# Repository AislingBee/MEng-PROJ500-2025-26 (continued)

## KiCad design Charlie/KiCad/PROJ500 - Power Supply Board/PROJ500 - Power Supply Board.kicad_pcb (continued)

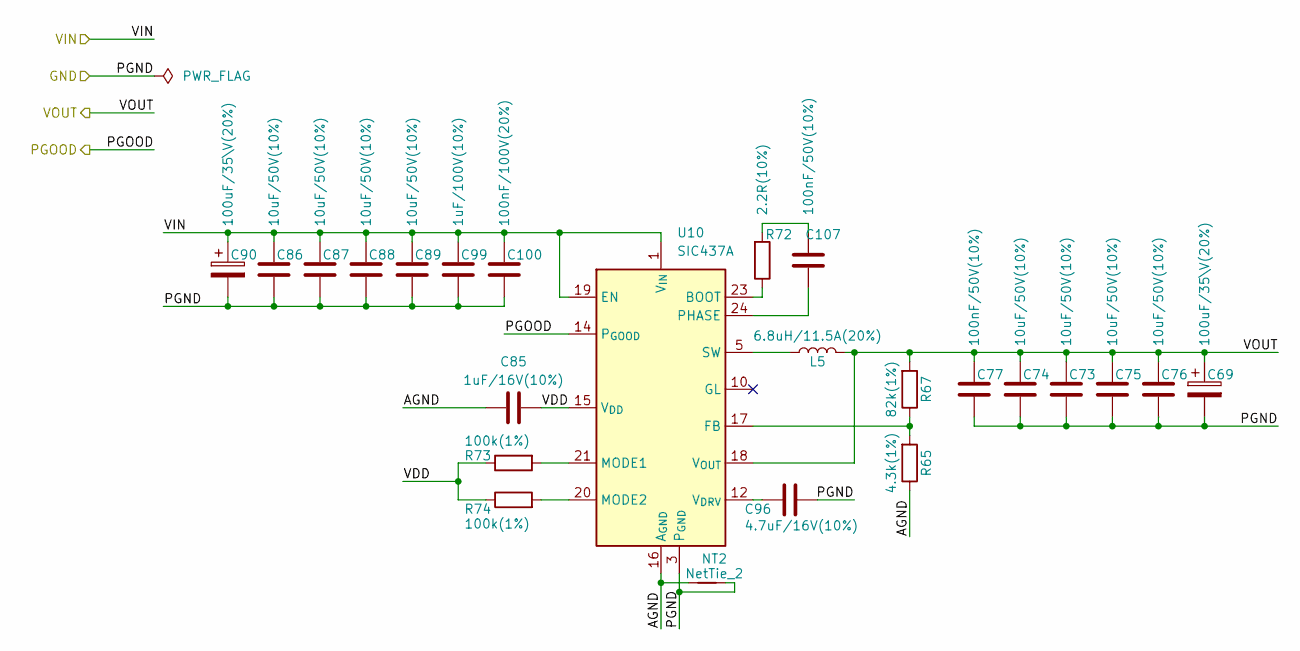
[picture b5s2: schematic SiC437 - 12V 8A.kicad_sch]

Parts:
C69, C90: 100uF/35\V(20%); CAPAE830X700N
C73, C74, C75, C76, C86, C87, C88, C89: 10uF/50V(10%); C_1206_3216Metric
C77, C107: 100nF/50V(10%); C_0402_1005Metric
C85: 1uF/16V(10%); C_0603_1608Metric
C96: 4.7uF/16V(10%); C_0805_2012Metric
C99: 1uF/100V(10%); C_0603_1608Metric
C100: 100nF/100V(20%); C_0603_1608Metric
L5: 6.8uH/11.5A(20%); INDPM135125X650N
NT2: NetTie_2; NetTie-2_SMD_Pad0.5mm
R65: 4.3k(1%); R_0402_1005Metric
R67: 82k(1%); R_0402_1005Metric
R72: 2.2R(10%); R_0402_1005Metric
R73, R74: 100k(1%); R_0402_1005Metric
U10: SIC437A; Vishay_PowerPAK_MLP44-24L

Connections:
24V_SW: C86.1, C87.1, C88.1, C89.1, C90.1, C99.1, C100.1, U10.1 (V_{IN}), U10.2 (V_{IN}), U10.19 (EN), U10.22 (V_{IN}), U10.26 (V_{IN}); also elsewhere on the board
/12V_SW_PGOOD: U10.14 (P_{GOOD}); also elsewhere on the board
/I_12V_SW_P: C69.1, C73.1, C74.1, C75.1, C76.1, C77.1, L5.2, R67.2, U10.18 (V_{OUT}); also elsewhere on the board
/SiC437 - 12V 8A/AGND: C85.1, NT2.1, R65.1, U10.16 (A_{GND}), U10.25 (A_{GND})
/SiC437 - 12V 8A/VDD: C85.2, R73.1, R74.1, U10.15 (V_{DD})
GNDPWR: C69.2, C73.2, C74.2, C75.2, C76.2, C77.2, C86.2, C87.2, C88.2, C89.2, C90.2, C96.2, C99.2, C100.2, NT2.2, U10.3 (P_{GND}), U10.4 (P_{GND}), U10.13 (P_{GND}), U10.27 (P_{GND}); also elsewhere on the board
unnamed: C107.2, R72.2
unnamed: L5.1, U10.5 (SW), U10.6 (SW), U10.7 (SW), U10.8 (SW), U10.9 (SW)
unnamed: R72.1, U10.23 (BOOT)
unnamed: R65.2, R67.1, U10.17 (FB)
unnamed: R73.2, U10.21 (MODE1)
unnamed: R74.2, U10.20 (MODE2)
unnamed: C107.1, U10.24 (PHASE)
unnamed: C96.1, U10.12 (V_{DRV})

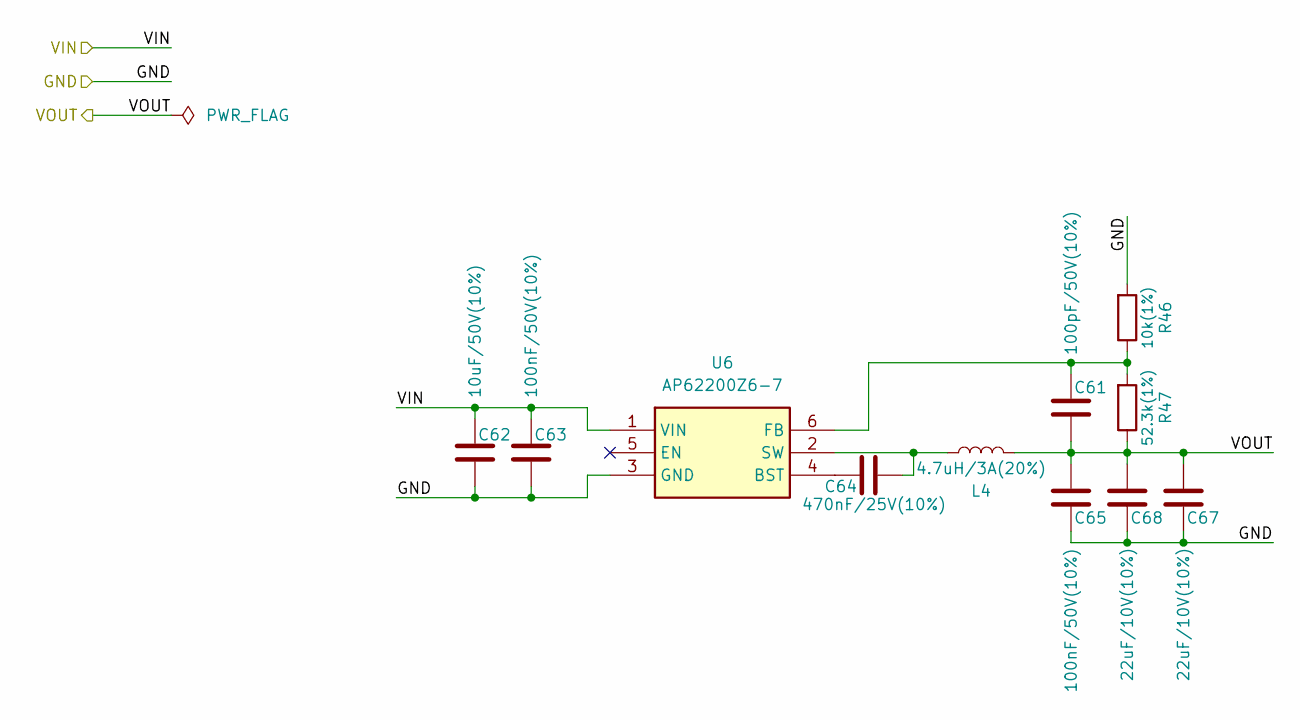
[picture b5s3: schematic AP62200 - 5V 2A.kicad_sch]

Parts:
C61: 100pF/50V(10%); C_0402_1005Metric
C62: 10uF/50V(10%); C_1206_3216Metric
C63, C65: 100nF/50V(10%); C_0402_1005Metric
C64: 470nF/25V(10%); C_0603_1608Metric
C67, C68: 22uF/10V(10%); C_0805_2012Metric
L4: 4.7uH/3A(20%); ASPI-4030S
R46: 10k(1%); R_0402_1005Metric
R47: 52.3k(1%); R_0402_1005Metric
U6: AP62200Z6-7; SOT-563; Mouser Part Number 621-AP62200Z6-7

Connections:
+5V: C61.2, C65.1, C67.1, C68.1, L4.1, R47.1; also elsewhere on the board
+12V: C62.1, C63.1, U6.1 (VIN); also elsewhere on the board
GNDPWR: C62.2, C63.2, C65.2, C67.2, C68.2, R46.2, U6.3 (GND); also elsewhere on the board
unnamed: C64.1, U6.4 (BST)
unnamed: C61.1, R46.1, R47.2, U6.6 (FB)
unnamed: C64.2, L4.2, U6.2 (SW)

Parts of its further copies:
C84, C93: 22uF/10V(10%); C_0805_2012Metric
C91: 10uF/50V(10%); C_1206_3216Metric
C98, C102: 100nF/50V(10%); C_0402_1005Metric
C109: 100pF/50V(10%); C_0402_1005Metric
C110: 470nF/25V(10%); C_0603_1608Metric
L6: 4.7uH/3A(20%); ASPI-4030S
R70: 10k(1%); R_0402_1005Metric
R80: 52.3k(1%); R_0402_1005Metric
U13: AP62200Z6-7; SOT-563; Mouser Part Number 621-AP62200Z6-7

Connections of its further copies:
5V_SW: C84.1, C93.1, C98.1, C109.2, L6.1, R80.1; also elsewhere on the board
12V_SW: C91.1, C102.1, U13.1 (VIN); also elsewhere on the board
GNDPWR: C84.2, C91.2, C93.2, C98.2, C102.2, R70.2, U13.3 (GND); also elsewhere on the board
unnamed: C110.1, U13.4 (BST)
unnamed: C109.1, R70.1, R80.2, U13.6 (FB)
unnamed: C110.2, L6.2, U13.2 (SW)

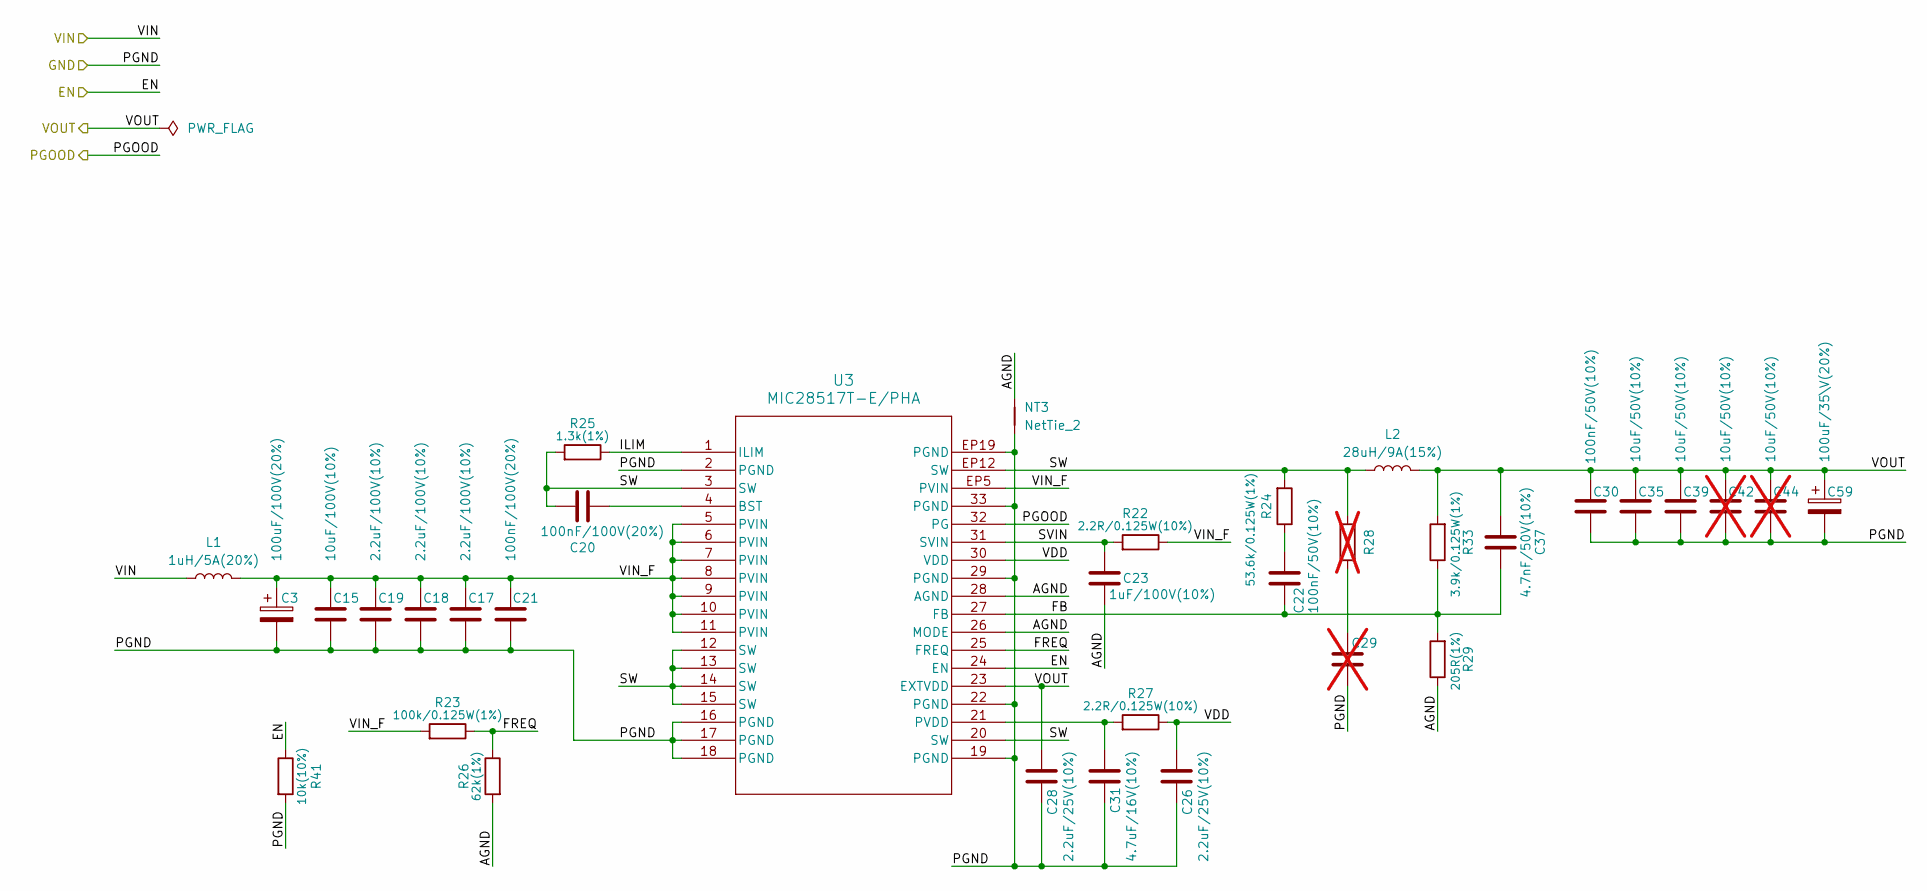
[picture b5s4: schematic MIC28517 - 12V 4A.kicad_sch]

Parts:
C3: 100uF/100V(20%); CP_Radial_D10.0mm_P5.00mm
C15: 10uF/100V(10%); C_1210_3225Metric
C17, C18, C19: 2.2uF/100V(10%); C_0805_2012Metric
C20, C21: 100nF/100V(20%); C_0603_1608Metric
C22, C30: 100nF/50V(10%); C_0402_1005Metric
C23: 1uF/100V(10%); C_0603_1608Metric
C26, C28: 2.2uF/25V(10%); C_0805_2012Metric
C29: C_0603_1608Metric; not fitted
C31: 4.7uF/16V(10%); C_0805_2012Metric
C35, C39: 10uF/50V(10%); C_1206_3216Metric
C37: 4.7nF/50V(10%); C_0402_1005Metric
C42, C44: 10uF/50V(10%); C_1206_3216Metric; not fitted
C59: 100uF/35\V(20%); CAPAE830X700N
L1: 1uH/5A(20%); L_1008_2520Metric
L2: 28uH/9A(15%); PA2729283NL
NT3: NetTie_2; NetTie-2_SMD_Pad0.5mm
R22: 2.2R/0.125W(10%); R_0805_2012Metric
R23: 100k/0.125W(1%); R_0603_1608Metric
R24: 53.6k/0.125W(1%); R_0805_2012Metric
R25: 1.3k(1%); R_0402_1005Metric
R26: 62k(1%); R_0402_1005Metric
R27: 2.2R/0.125W(10%); R_0603_1608Metric
R28: R_0805_2012Metric; not fitted
R29: 205R(1%); R_0402_1005Metric
R33: 3.9k/0.125W(1%); R_0603_1608Metric
R41: 10k(10%); R_0402_1005Metric
U3: MIC28517T-E/PHA; VQFN32_6X6_3EP_PHA_MCH

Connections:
+12V: C28.2, C30.1, C35.1, C37.2, C39.1, C42.1, C44.1, C59.1, L2.1, R33.2, U3.23 (EXTVDD); also elsewhere on the board
/12V_PGOOD: U3.32 (PG); also elsewhere on the board
/AON_EN: R41.1, U3.24 (EN); also elsewhere on the board
/MIC28517 - 12V 4A/AGND: C23.2, NT3.2, R26.2, R29.1, U3.26 (MODE), U3.28 (AGND)
/MIC28517 - 12V 4A/FB: C22.2, C37.1, R29.2, R33.1, U3.27 (FB)
/MIC28517 - 12V 4A/FREQ: R23.1, R26.1, U3.25 (FREQ)
/MIC28517 - 12V 4A/ILIM: R25.1, U3.1 (ILIM)
/MIC28517 - 12V 4A/SVIN: C23.1, R22.2, U3.31 (SVIN)
/MIC28517 - 12V 4A/SW: C20.1, L2.2, R24.2, R25.2, R28.2, U3.3 (SW), U3.12 (SW), U3.13 (SW), U3.14 (SW), U3.15 (SW), U3.20 (SW), U3.EP12 (SW)
/MIC28517 - 12V 4A/VDD: C26.2, R27.1, U3.30 (VDD)
/MIC28517 - 12V 4A/VIN_F: C3.1, C15.1, C17.1, C18.1, C19.1, C21.1, L1.2, R22.1, R23.2, U3.5 (PVIN), U3.6 (PVIN), U3.7 (PVIN), U3.8 (PVIN), U3.9 (PVIN), U3.10 (PVIN), U3.11 (PVIN), U3.EP5 (PVIN)
GNDPWR: C3.2, C15.2, C17.2, C18.2, C19.2, C21.2, C26.1, C28.1, C29.2, C30.2, C31.1, C35.2, C39.2, C42.2, C44.2, C59.2, NT3.1, R41.2, U3.2 (PGND), U3.16 (PGND), U3.17 (PGND), U3.18 (PGND), U3.19 (PGND), U3.22 (PGND), U3.29 (PGND), U3.33 (PGND), U3.EP19 (PGND); also elsewhere on the board
unnamed: C22.1, R24.1
unnamed: C29.1, R28.1
unnamed: C20.2, U3.4 (BST)
unnamed: C31.2, R27.2, U3.21 (PVDD)
VRAW: L1.1; also elsewhere on the board

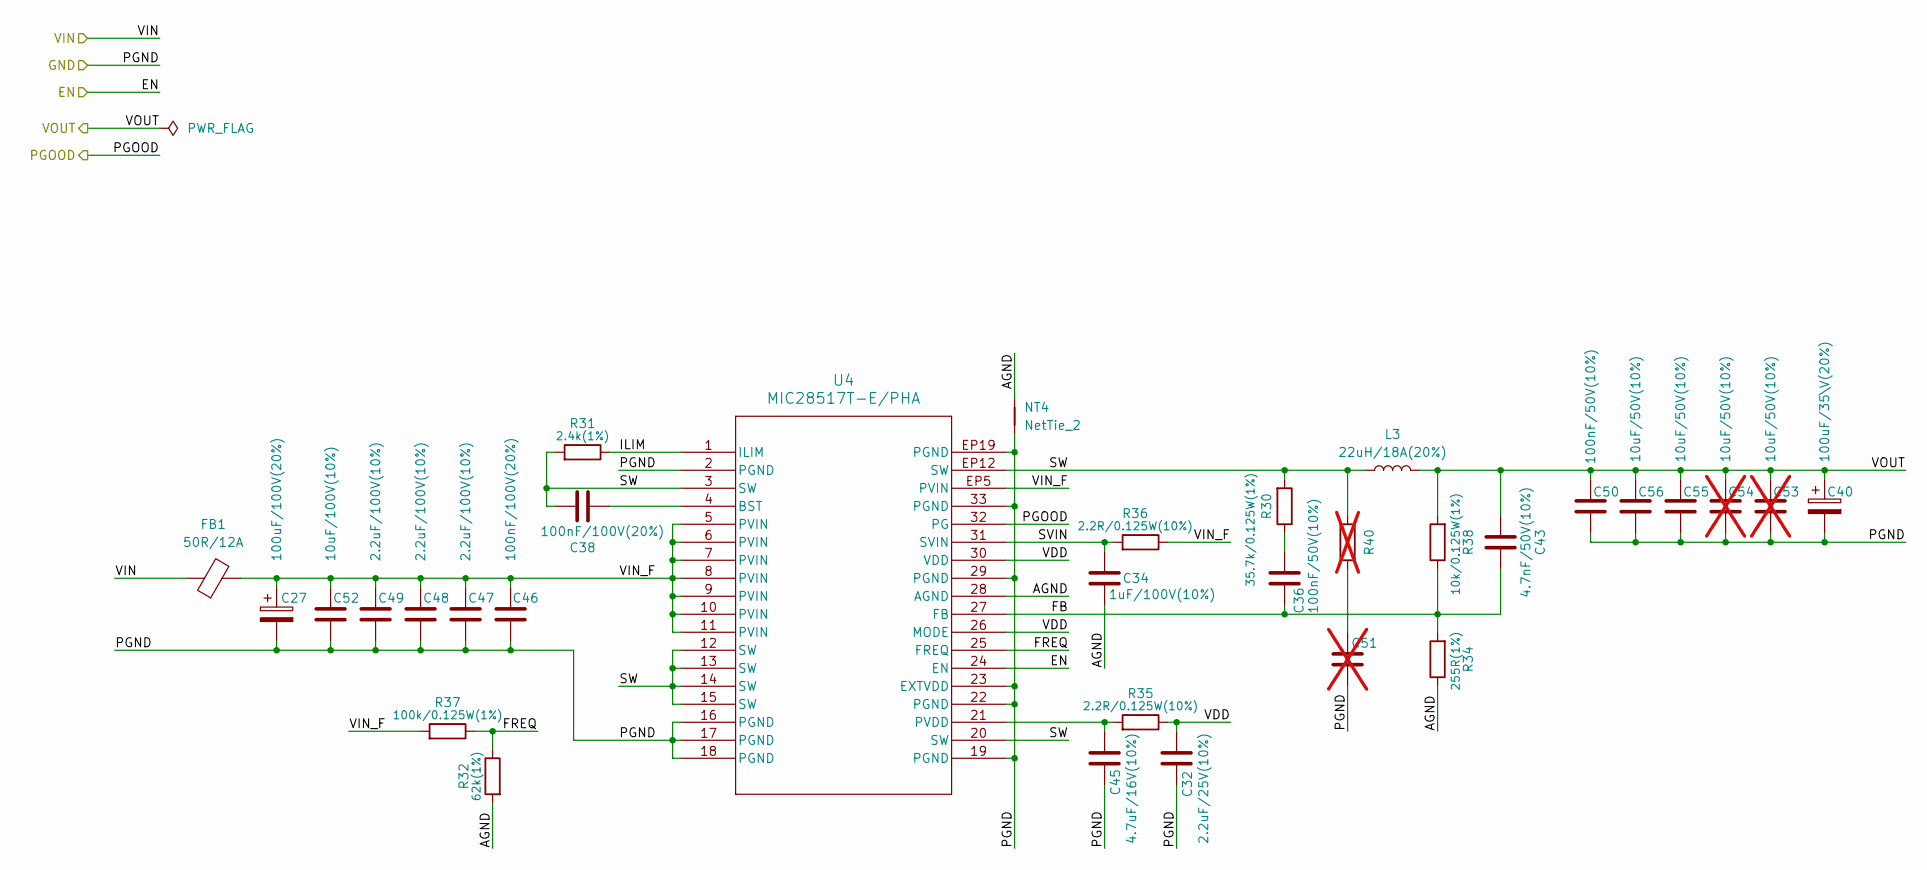
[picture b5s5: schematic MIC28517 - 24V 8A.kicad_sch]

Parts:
C27: 100uF/100V(20%); CP_Radial_D10.0mm_P5.00mm
C32: 2.2uF/25V(10%); C_0805_2012Metric
C34: 1uF/100V(10%); C_0603_1608Metric
C36, C50: 100nF/50V(10%); C_0402_1005Metric
C38, C46: 100nF/100V(20%); C_0603_1608Metric
C40: 100uF/35\V(20%); CAPAE830X700N
C43: 4.7nF/50V(10%); C_0402_1005Metric
C45: 4.7uF/16V(10%); C_0805_2012Metric
C47, C48, C49: 2.2uF/100V(10%); C_0805_2012Metric
C51: C_0603_1608Metric; not fitted
C52: 10uF/100V(10%); C_1210_3225Metric
C53, C54: 10uF/50V(10%); C_1206_3216Metric; not fitted
C55, C56: 10uF/50V(10%); C_1206_3216Metric
FB1: 50R/12A; L_1206_3216Metric
L3: 22uH/18A(20%); PA2247.223NLT
NT4: NetTie_2; NetTie-2_SMD_Pad0.5mm
R30: 35.7k/0.125W(1%); R_0805_2012Metric
R31: 2.4k(1%); R_0402_1005Metric
R32: 62k(1%); R_0402_1005Metric
R34: 255R(1%); R_0402_1005Metric
R35: 2.2R/0.125W(10%); R_0603_1608Metric
R36: 2.2R/0.125W(10%); R_0805_2012Metric
R37: 100k/0.125W(1%); R_0603_1608Metric
R38: 10k/0.125W(1%); R_0603_1608Metric
R40: R_0805_2012Metric; not fitted
U4: MIC28517T-E/PHA; VQFN32_6X6_3EP_PHA_MCH

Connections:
/24V_SW_PGOOD: U4.32 (PG); also elsewhere on the board
/I_24V_SW_P: C40.1, C43.2, C50.1, C53.1, C54.1, C55.1, C56.1, L3.1, R38.2; also elsewhere on the board
/MIC28517 - 24V 8A/AGND: C34.2, NT4.2, R32.2, R34.1, U4.28 (AGND)
/MIC28517 - 24V 8A/FB: C36.2, C43.1, R34.2, R38.1, U4.27 (FB)
/MIC28517 - 24V 8A/FREQ: R32.1, R37.1, U4.25 (FREQ)
/MIC28517 - 24V 8A/ILIM: R31.1, U4.1 (ILIM)
/MIC28517 - 24V 8A/SVIN: C34.1, R36.2, U4.31 (SVIN)
/MIC28517 - 24V 8A/SW: C38.1, L3.2, R30.2, R31.2, R40.2, U4.3 (SW), U4.12 (SW), U4.13 (SW), U4.14 (SW), U4.15 (SW), U4.20 (SW), U4.EP12 (SW)
/MIC28517 - 24V 8A/VDD: C32.2, R35.1, U4.26 (MODE), U4.30 (VDD)
/MIC28517 - 24V 8A/VIN_F: C27.1, C46.1, C47.1, C48.1, C49.1, C52.1, FB1.2, R36.1, R37.2, U4.5 (PVIN), U4.6 (PVIN), U4.7 (PVIN), U4.8 (PVIN), U4.9 (PVIN), U4.10 (PVIN), U4.11 (PVIN), U4.EP5 (PVIN)
/SW_PGOOD: U4.24 (EN); also elsewhere on the board
GNDPWR: C27.2, C32.1, C40.2, C45.1, C46.2, C47.2, C48.2, C49.2, C50.2, C51.2, C52.2, C53.2, C54.2, C55.2, C56.2, NT4.1, U4.2 (PGND), U4.16 (PGND), U4.17 (PGND), U4.18 (PGND), U4.19 (PGND), U4.22 (PGND), U4.23 (EXTVDD), U4.29 (PGND), U4.33 (PGND), U4.EP19 (PGND); also elsewhere on the board
unnamed: C36.1, R30.1
unnamed: C51.1, R40.1
unnamed: C38.2, U4.4 (BST)
unnamed: C45.2, R35.2, U4.21 (PVDD)
VRAW_SW: FB1.1; also elsewhere on the board

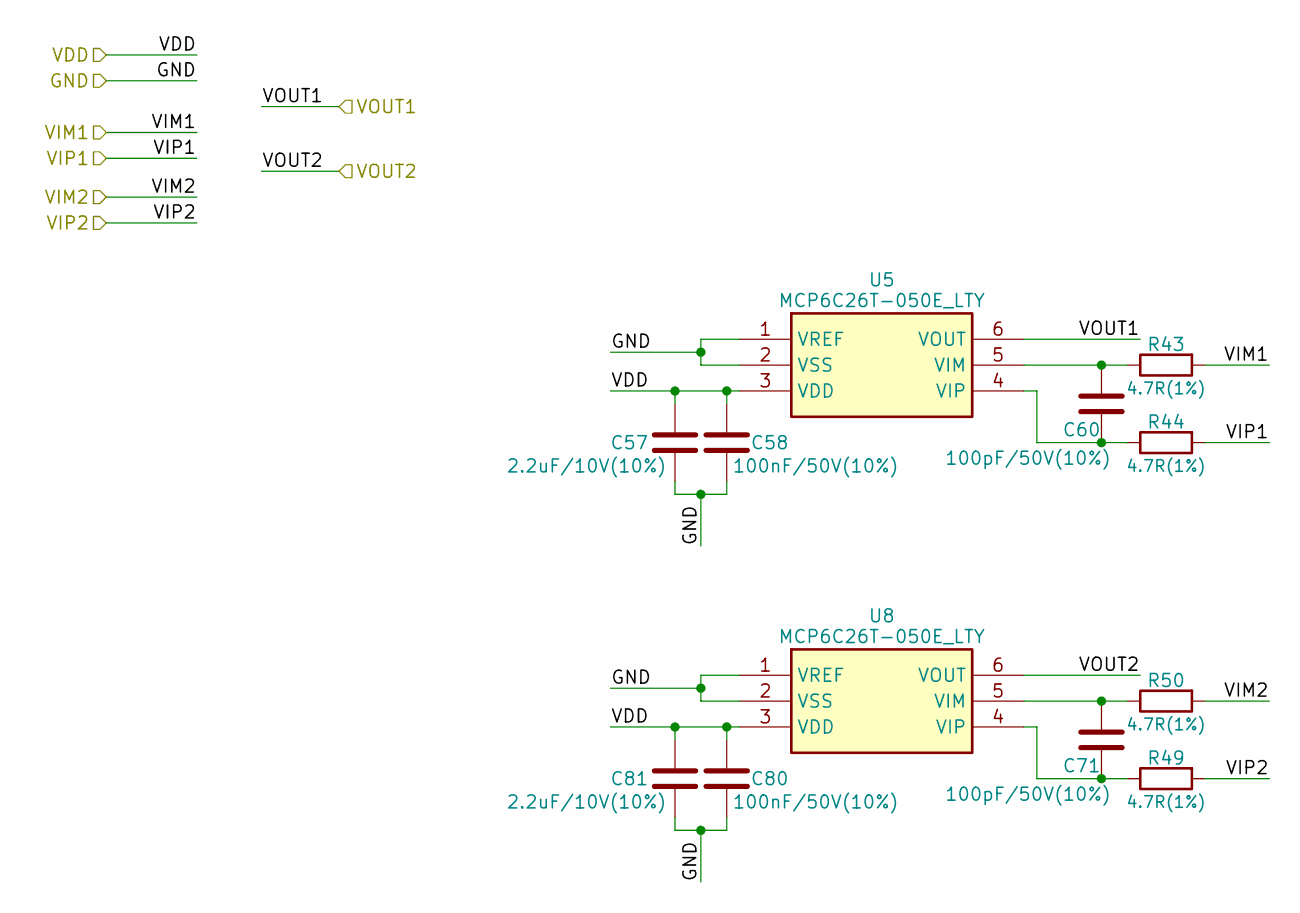
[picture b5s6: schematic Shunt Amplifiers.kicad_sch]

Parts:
C57, C81: 2.2uF/10V(10%); C_0603_1608Metric
C58, C80: 100nF/50V(10%); C_0402_1005Metric
C60, C71: 100pF/50V(10%); C_0402_1005Metric
R43, R44, R49, R50: 4.7R(1%); R_0402_1005Metric
U5, U8: MCP6C26T-050E_LTY; SOT-363_SC-70-6; Manufacturer_Part_Number MCP6C26T-050E/LTY

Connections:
12V_SW: R50.2; also elsewhere on the board
24V_SW: R43.2; also elsewhere on the board
+3.3V: C57.1, C58.1, C80.1, C81.1, U5.3 (VDD), U8.3 (VDD); also elsewhere on the board
/I_12V_SW: U8.6 (VOUT); also elsewhere on the board
/I_12V_SW_P: R49.2; also elsewhere on the board
/I_24V_SW: U5.6 (VOUT); also elsewhere on the board
/I_24V_SW_P: R44.2; also elsewhere on the board
GNDA: C57.2, C58.2, C80.2, C81.2, U5.1 (VREF), U5.2 (VSS), U8.1 (VREF), U8.2 (VSS); also elsewhere on the board
unnamed: C60.1, R43.1, U5.5 (VIM)
unnamed: C60.2, R44.1, U5.4 (VIP)
unnamed: C71.1, R50.1, U8.5 (VIM)
unnamed: C71.2, R49.1, U8.4 (VIP)

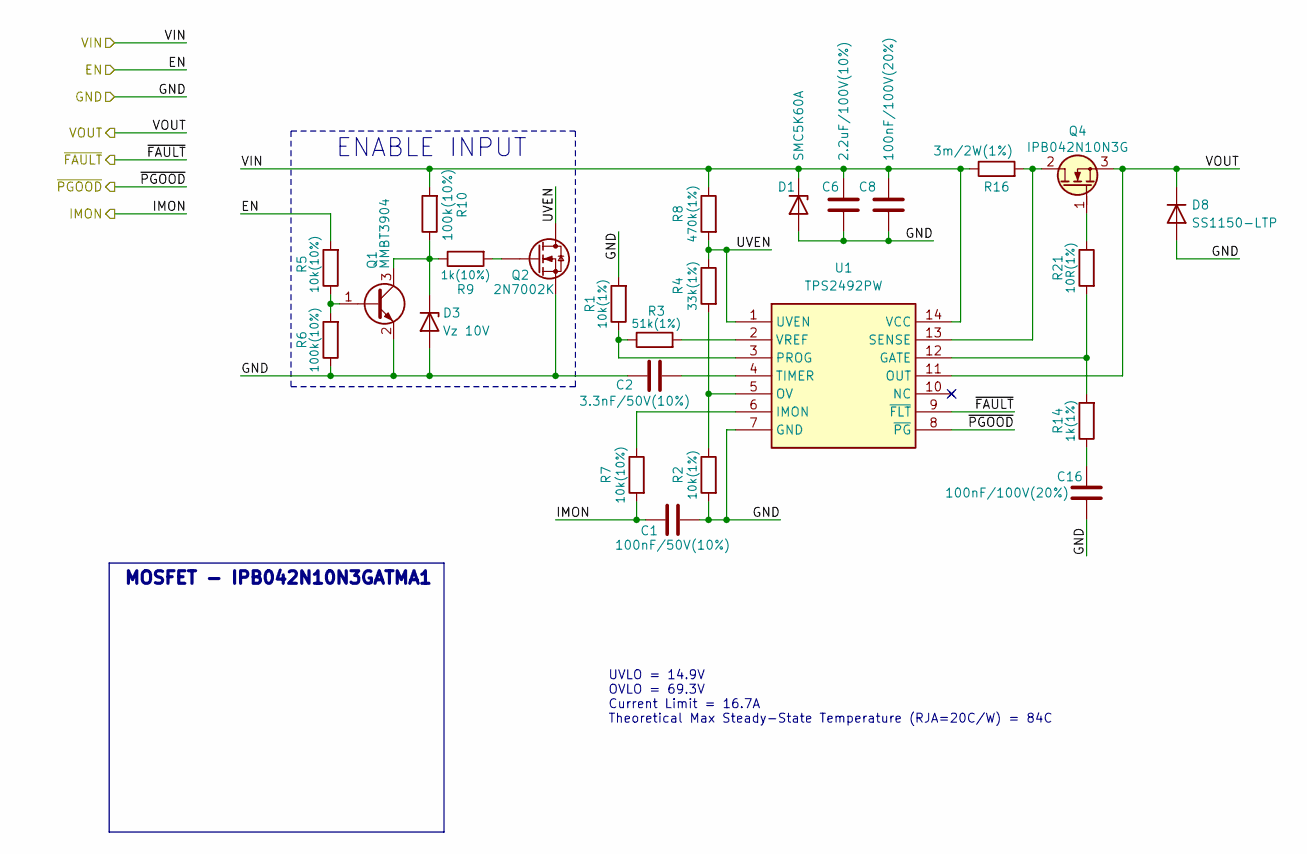
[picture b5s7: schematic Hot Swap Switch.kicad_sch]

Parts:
C1: 100nF/50V(10%); C_0402_1005Metric
C2: 3.3nF/50V(10%); C_0402_1005Metric
C6: 2.2uF/100V(10%); C_0805_2012Metric
C8, C16: 100nF/100V(20%); C_0603_1608Metric
D1: SMC5K60A; D_SMC
D3: Vz 10V; D_SOD-323
D8: SS1150-LTP; D_SMA
Q1: MMBT3904; SOT-23
Q2: 2N7002K; SOT-23
Q4: IPB042N10N3G; TO-263-3_TabPin2
R1, R2: 10k(1%); R_0402_1005Metric
R3: 51k(1%); R_0402_1005Metric
R4: 33k(1%); R_0402_1005Metric
R5, R7: 10k(10%); R_0402_1005Metric
R6: 100k(10%); R_0402_1005Metric
R8: 470k(1%); R_0805_2012Metric
R9: 1k(10%); R_0402_1005Metric
R10: 100k(10%); R_0805_2012Metric
R14: 1k(1%); R_0805_2012Metric
R16: 3m/2W(1%); R_2512_6332Metric
R21: 10R(1%); R_0603_1608Metric
U1: TPS2492PW; TSSOP-14_4.4x5mm_P0.65mm; Mouser Part Number 595-TPS2492PW

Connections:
/Hot Swap Switch/UVEN: Q2.3 (D), R4.1, R8.2, U1.1 (UVEN)
/SW_EN: R5.2; also elsewhere on the board
/SW_IMON: C1.1, R7.2; also elsewhere on the board
/~SW_FAULT: U1.9 (~FLT); also elsewhere on the board
/~SW_PGOOD: U1.8 (~PG); also elsewhere on the board
GNDPWR: C1.2, C2.2, C6.2, C8.1, C16.1, D1.2 (A), D3.2 (A), D8.2 (A), Q1.2 (E), Q2.2 (S), R1.2, R2.2, R6.1, U1.7 (GND); also elsewhere on the board
unnamed: C16.2, R14.1
unnamed: D3.1 (K), Q1.3 (C), R9.1, R10.1
unnamed: Q1.1 (B), R5.1, R6.2
unnamed: Q2.1 (G), R9.2
unnamed: Q4.2 (D), R16.2, U1.13 (SENSE)
unnamed: Q4.1 (G), R21.1
unnamed: R14.2, R21.2, U1.12 (GATE)
unnamed: R7.1, U1.6 (IMON)
unnamed: R2.1, R4.2, U1.5 (OV)
unnamed: R1.1, R3.1, U1.3 (PROG)
unnamed: C2.1, U1.4 (TIMER)
unnamed: R3.2, U1.2 (VREF)
VRAW: C6.1, C8.2, D1.1 (K), R8.1, R10.2, R16.1, U1.14 (VCC); also elsewhere on the board
VRAW_SW: D8.1 (K), Q4.3 (S), U1.11 (OUT); also elsewhere on the board

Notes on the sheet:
ENABLE INPUT
UVLO = 14.9V OVLO = 69.3V Current Limit = 16.7A Theoretical Max Steady-State Temperature (RJA=20C/W) = 84C
MOSFET - IPB042N10N3GATMA1

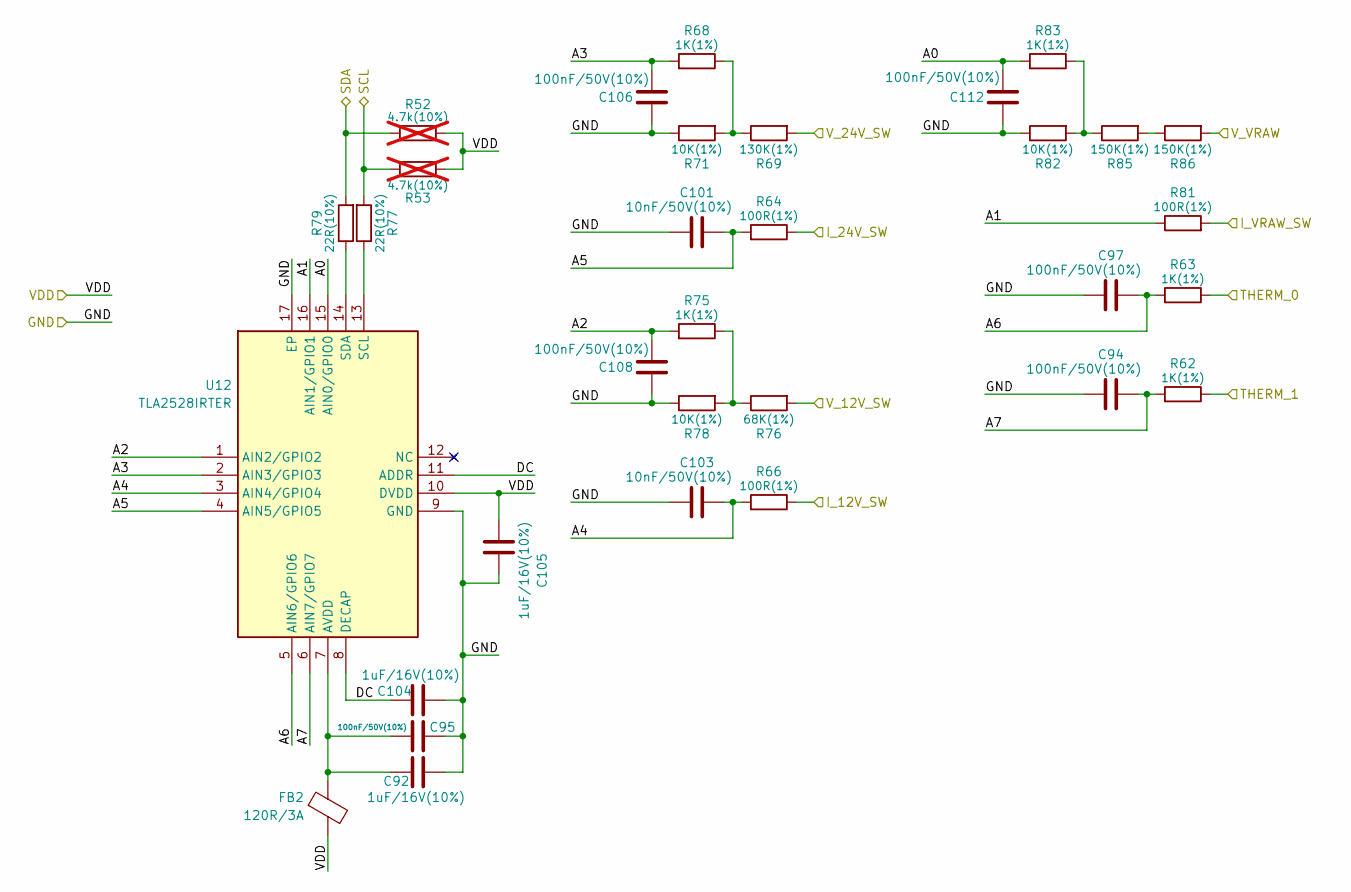
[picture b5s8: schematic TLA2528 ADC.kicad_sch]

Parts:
C92, C104, C105: 1uF/16V(10%); C_0603_1608Metric
C94, C95, C97, C106, C108, C112: 100nF/50V(10%); C_0402_1005Metric
C101, C103: 10nF/50V(10%); C_0402_1005Metric
FB2: 120R/3A; L_0603_1608Metric
R52, R53: 4.7k(10%); R_0402_1005Metric; not fitted
R62, R63, R68, R75, R83: 1K(1%); R_0402_1005Metric
R64, R66, R81: 100R(1%); R_0402_1005Metric
R69: 130K(1%); R_0402_1005Metric
R71, R78, R82: 10K(1%); R_0402_1005Metric
R76: 68K(1%); R_0402_1005Metric
R77, R79: 22R(10%); R_0402_1005Metric
R85, R86: 150K(1%); R_0402_1005Metric
U12: TLA2528IRTER; WQFN-16-1EP_3x3mm_P0.5mm_EP1.75x1.75mm; Mouser Part Number 595-TLA2528IRTER

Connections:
12V_SW: R76.2; also elsewhere on the board
24V_SW: R69.2; also elsewhere on the board
+3.3V: C105.2, FB2.2, R52.1, R53.2, U12.10 (DVDD); also elsewhere on the board
/I_12V_SW: R66.1; also elsewhere on the board
/I_24V_SW: R64.1; also elsewhere on the board
/SCL: R53.1, R77.2; also elsewhere on the board
/SDA: R52.2, R79.2; also elsewhere on the board
/SW_IMON: R81.2; also elsewhere on the board
/THERM_0: R63.1; also elsewhere on the board
/THERM_1: R62.1; also elsewhere on the board
/TLA2528 ADC/A0: C112.1, R83.2, U12.15 (AIN0/GPIO0)
/TLA2528 ADC/A1: R81.1, U12.16 (AIN1/GPIO1)
/TLA2528 ADC/A2: C108.1, R75.2, U12.1 (AIN2/GPIO2)
/TLA2528 ADC/A3: C106.1, R68.2, U12.2 (AIN3/GPIO3)
/TLA2528 ADC/A4: C103.2, R66.2, U12.3 (AIN4/GPIO4)
/TLA2528 ADC/A5: C101.2, R64.2, U12.4 (AIN5/GPIO5)
/TLA2528 ADC/A6: C97.2, R63.2, U12.5 (AIN6/GPIO6)
/TLA2528 ADC/A7: C94.2, R62.2, U12.6 (AIN7/GPIO7)
/TLA2528 ADC/DC: C104.1, U12.8 (DECAP), U12.11 (ADDR)
GNDA: C92.2, C94.1, C95.2, C97.1, C101.1, C103.1, C104.2, C105.1, C106.2, C108.2, C112.2, R71.1, R78.1, R82.1, U12.9 (GND), U12.17 (EP); also elsewhere on the board
unnamed: R68.1, R69.1, R71.2
unnamed: R75.1, R76.1, R78.2
unnamed: R82.2, R83.1, R85.1
unnamed: R85.2, R86.1
unnamed: C92.1, C95.1, FB2.1, U12.7 (AVDD)
unnamed: R77.1, U12.13 (SCL)
unnamed: R79.1, U12.14 (SDA)
VRAW: R86.2; also elsewhere on the board

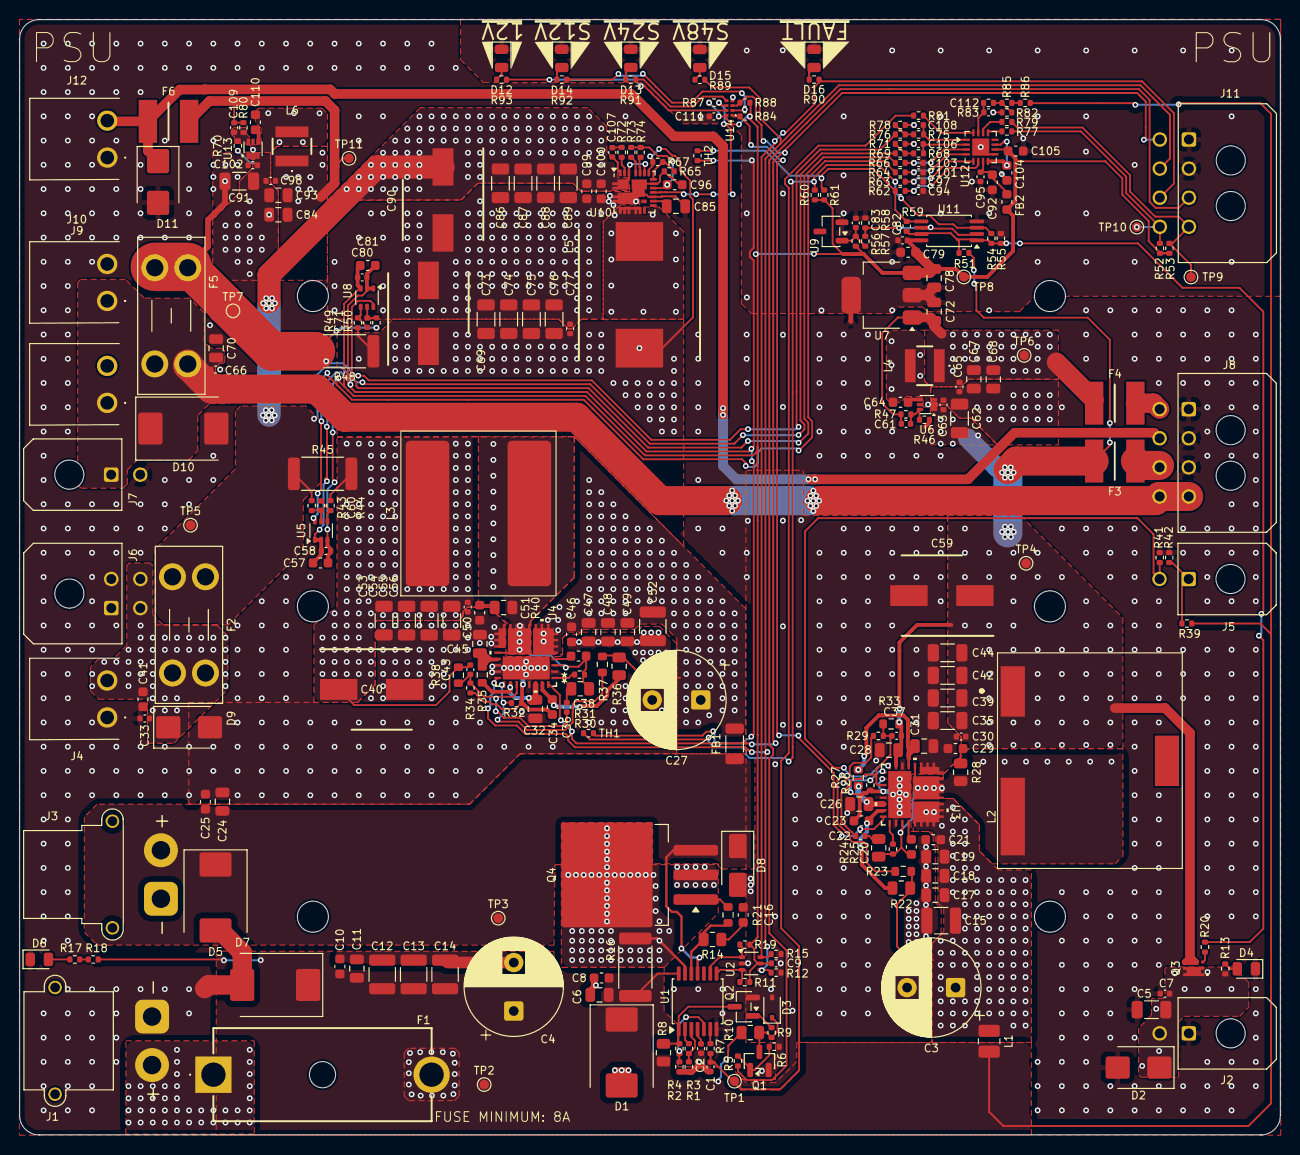
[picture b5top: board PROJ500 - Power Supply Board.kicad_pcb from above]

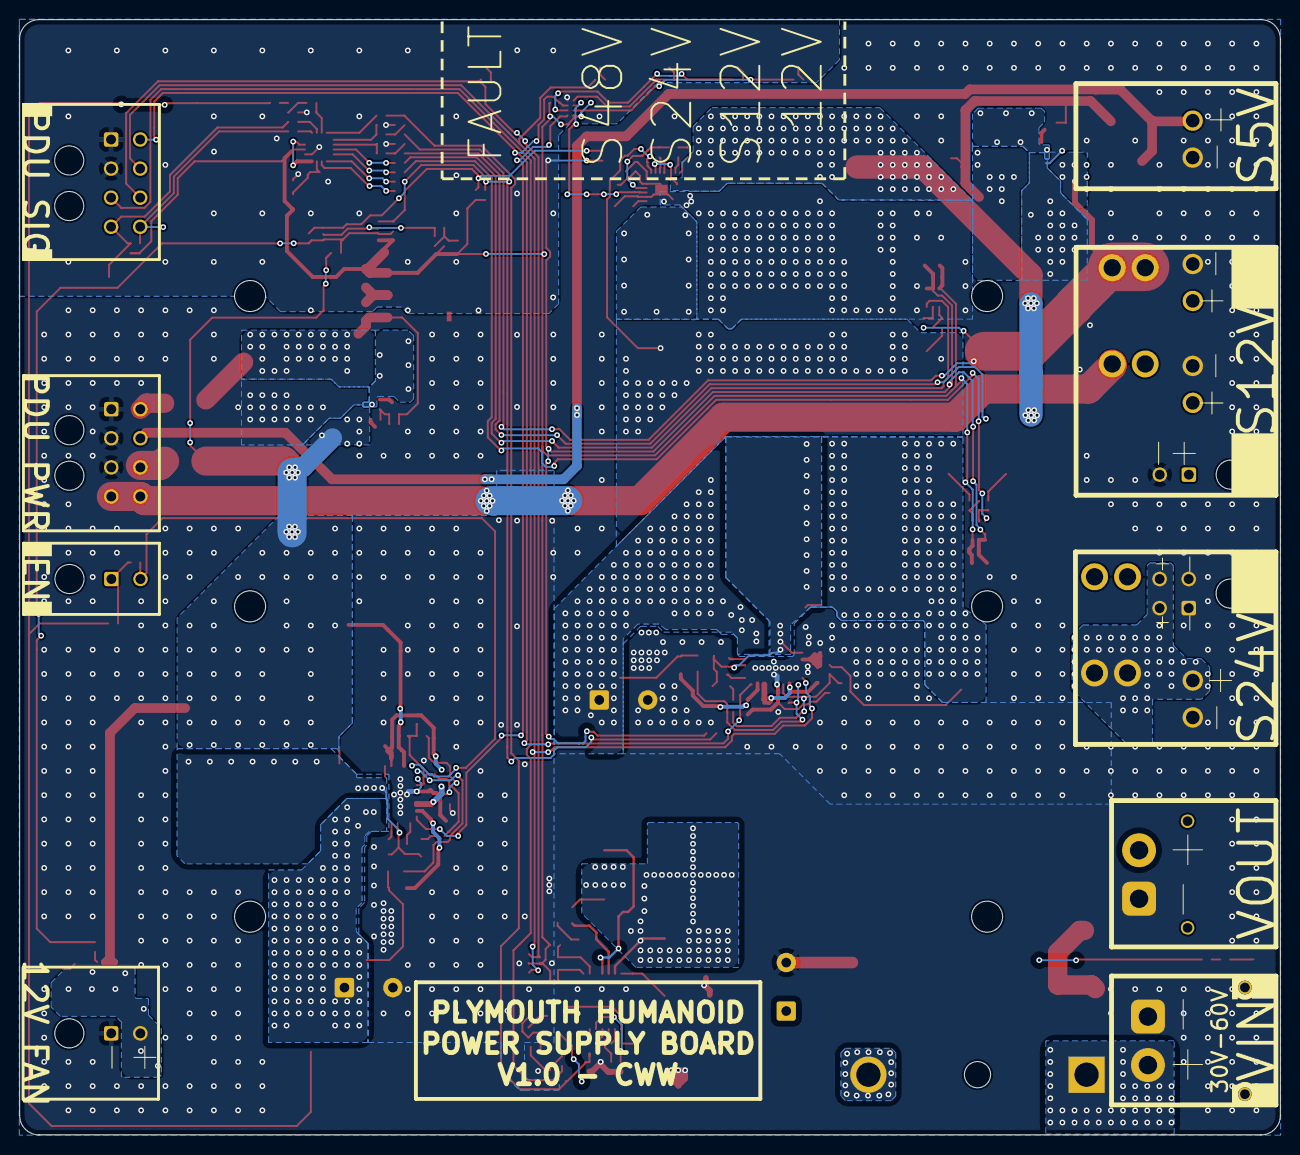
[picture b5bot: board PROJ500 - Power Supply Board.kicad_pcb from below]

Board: 2 copper layers, 130.0 x 115.0 mm, 288 parts (2 on the bottom side), 124 nets.

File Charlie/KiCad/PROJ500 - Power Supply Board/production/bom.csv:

Designator,Footprint,Quantity,Value,LCSC Part #
"C1, C102, C106, C107, C108, C111, C112, C22, C30, C33, C36, C50, C58, C63, C65, C66, C7, C77, C80, C82, C83, C9, C94, C95, C97, C98",0402,26,100nF/50V(10%),
"C10, C100, C16, C20, C21, C25, C38, C46, C8",0603,9,100nF/100V(20%),
"C101, C103",0402,2,10nF/50V(10%),
"C104, C105, C85, C92",0603,4,1uF/16V(10%),
"C109, C60, C61, C71",0402,4,100pF/50V(10%),
"C11, C17, C18, C19, C24, C47, C48, C49, C6",0805,9,2.2uF/100V(10%),
"C110, C64",0603,2,470nF/25V(10%),
"C12, C13, C14, C15, C52",1210,5,10uF/100V(10%),
C2,0402,1,3.3nF/50V(10%),
"C23, C34, C41, C99",0603,4,1uF/100V(10%),
"C26, C28, C32, C70",0805,4,2.2uF/25V(10%),
"C27, C3, C4",CP_Radial_D10.0mm_P5.00mm,3,100uF/100V(20%),
"C31, C45, C72, C78, C96",0805,5,4.7uF/16V(10%),
"C35, C39, C5, C55, C56, C62, C73, C74, C75, C76, C86, C87, C88, C89, C91",1206,15,10uF/50V(10%),
"C37, C43",0402,2,4.7nF/50V(10%),
"C40, C59, C69, C90",CAPAE830X700N,4,100uF/35\V(20%),
"C57, C81",0603,2,2.2uF/10V(10%),
"C67, C68, C84, C93",0805,4,22uF/10V(10%),
C79,0603,1,1uF/25V(10%),
"D1, D5, D7",D_SMC,3,SMC5K60A,
D10,D_SMC,1,SMCJ15A,
D11,D_SMB,1,SMBJ6.0A,
D12,0805,1,GR_12V_PGOOD,
D13,0805,1,GR_24V_SW_PGOOD,
D14,0805,1,GR_12V_SW_PGOOD,
D15,0805,1,GR_SW_PGOOD,
D16,0805,1,RED_SW_FAULT,
D2,D_SMB,1,VSSB410S,
D3,D_SOD-323,1,Vz 10V,
D4,0805,1,OR_FAN,
D6,0805,1,OR_VRAW_PRESENT,
D8,D_SMA,1,SS1150-LTP,
D9,D_SMB,1,SMBJ26A,
F1,65600301009,1,3x20mm/8A,
"F2, F5",Fuseholder_Blade_Mini_Keystone_3568,2,MINI297/10A,
F3,FUSC5141X160N,1,2016L260/24MR,
"F4, F6",FUSC5141X160N,2,2016L300/16MR,
FB1,1206,1,50R/12A,
FB2,0603,1,120R/3A,
J1,AMASS_XT30PW-M_1x02_P2.50mm_Horizontal,1,VRAW,
"J10, J9",TBP02R138102BE,2,12V_SW,
J11,Molex_Micro-Fit_3.0_43045-0800_2x04_P3.00mm_Horizontal,1,B2B_SIG,
J12,TBP02R138102BE,1,5V_SW,
J2,Molex_Micro-Fit_3.0_43045-0200_2x01_P3.00mm_Horizontal,1,12V_FAN,
J3,AMASS_XT30PW-F_1x02_P2.50mm_Horizontal,1,VRAW_SW,
J4,TBP02R138102BE,1,24V_SW,
J5,Molex_Micro-Fit_3.0_43045-0200_2x01_P3.00mm_Horizontal,1,EN,
J6,Molex_Micro-Fit_3.0_43045-0400_2x02_P3.00mm_Horizontal,1,24V_SW,
J7,Molex_Micro-Fit_3.0_43045-0200_2x01_P3.00mm_Horizontal,1,12V_SW,
J8,Molex_Micro-Fit_3.0_43045-0800_2x04_P3.00mm_Horizontal,1,B2B_PWR,
L1,1008,1,1uH/5A(20%),
L2,PA2729283NL,1,28uH/9A(15%),
L3,PA2247.223NLT,1,22uH/18A(20%),
"L4, L6",ASPI-4030S,2,4.7uH/3A(20%),
L5,INDPM135125X650N,1,6.8uH/11.5A(20%),
Q1,SOT-23,1,MMBT3904,
Q2,SOT-23,1,2N7002K,
Q3,SIA469DJT1GE3,1,SIA469DJ,
Q4,TO-263-3_TabPin2,1,IPB042N10N3G,
"R1, R2, R46, R58, R60, R61, R70, R71, R78, R82",0402,10,10k(1%),
R10,0805,1,100k(10%),
"R11, R12, R13, R15, R19, R41, R5, R51, R7, R84, R87, R88",0402,12,10k(10%),
R14,0805,1,1k(1%),
R16,2512,1,3m/2W(1%),
"R17, R18",0402,2,27k(10%),
R20,0402,1,100R(10%),
R21,0603,1,10R(1%),
"R22, R36",0805,2,2.2R/0.125W(10%),
"R23, R37",0603,2,100k/0.125W(1%),
R24,0805,1,53.6k/0.125W(1%),
R25,0402,1,1.3k(1%),
"R26, R32",0402,2,62k(1%),
"R27, R35",0603,2,2.2R/0.125W(10%),
R29,0402,1,205R(1%),
R3,0402,1,51k(1%),
R30,0805,1,35.7k/0.125W(1%),
R31,0402,1,2.4k(1%),
R33,0603,1,3.9k/0.125W(1%),
R34,0402,1,255R(1%),
R38,0603,1,10k/0.125W(1%),
"R39, R42",0402,2,51k(10%),
R4,0402,1,33k(1%),
"R43, R44, R49, R50",0402,4,4.7R(1%),
"R45, R48",2512,2,5m/2W(1%),
"R47, R80",0402,2,52.3k(1%),
"R54, R59",0402,2,330k(10%),
"R56, R89, R9, R90, R91, R92, R93",0402,7,1k(10%),
R57,0402,1,13k(1%),
R6,0402,1,100k(10%),
"R62, R63, R68, R75, R83",0402,5,1K(1%),
"R64, R66, R81",0402,3,100R(1%),
R65,0402,1,4.3k(1%),
R67,0402,1,82k(1%),
R69,0402,1,130K(1%),
R72,0402,1,2.2R(10%),
"R73, R74",0402,2,100k(1%),
R76,0402,1,68K(1%),
"R77, R79",0402,2,22R(10%),
R8,0805,1,470k(1%),
"R85, R86",0402,2,150K(1%),
"TH1, TH2",0402,2,NTC/10K,
TP1,TestPoint_Pad_D1.0mm,1,I_VRAW_SW,
TP10,TestPoint_Pad_D1.0mm,1,SCL,
"TP11, TP6",TestPoint_Pad_D1.0mm,2,5V_SW,
TP2,TestPoint_Pad_D1.0mm,1,VRAW,
TP3,TestPoint_Pad_D1.0mm,1,VRAW_SW,
TP4,TestPoint_Pad_D1.0mm,1,12V,
TP5,TestPoint_Pad_D1.0mm,1,24V_SW,
TP7,TestPoint_Pad_D1.0mm,1,12V_SW,
TP8,TestPoint_Pad_D1.0mm,1,3.3V,
TP9,TestPoint_Pad_D1.0mm,1,SDA,
U1,TSSOP-14_4.4x5mm_P0.65mm,1,TPS2492PW,
U10,Vishay_PowerPAK_MLP44-24L,1,SIC437A,
U11,TSSOP-8_4.4x3mm_P0.65mm,1,LM393,
U12,WQFN-16-1EP_3x3mm_P0.5mm_EP1.75x1.75mm,1,TLA2528IRTER,
"U13, U6",SOT-563,2,AP62200Z6-7,
U14,XC7WT14GT115,1,"74LVC3G17GT,115",
U2,SOT-363_SC-70-6,1,74LVC2G14GW,
"U3, U4",VQFN32_6X6_3EP_PHA_MCH,2,MIC28517T-E/PHA,
"U5, U8",SOT-363_SC-70-6,2,MCP6C26T-050E_LTY,
U7,SOT-223,1,AP2114HA-3.3TRG1,
U9,SOT-23-3,1,2.5V,
